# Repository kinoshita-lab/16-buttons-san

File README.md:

# 16-buttons-san

## PCB with 16 buttons and shift registers

"16-buttons-san" is a handy PCB with 16 buttons, and shift resistors and can also cascade next same PCB.

## Kit contents

- Pre-assembled circuit board
- 1x5 pin socket

## How to assemble

Solder the included 1x05 pin socket into the following place below:

## Sample program

Please refer to the exapmles/Simple
<https://github.com/kinoshita-lab/16-buttons-san/tree/main/software/examples/Simple>

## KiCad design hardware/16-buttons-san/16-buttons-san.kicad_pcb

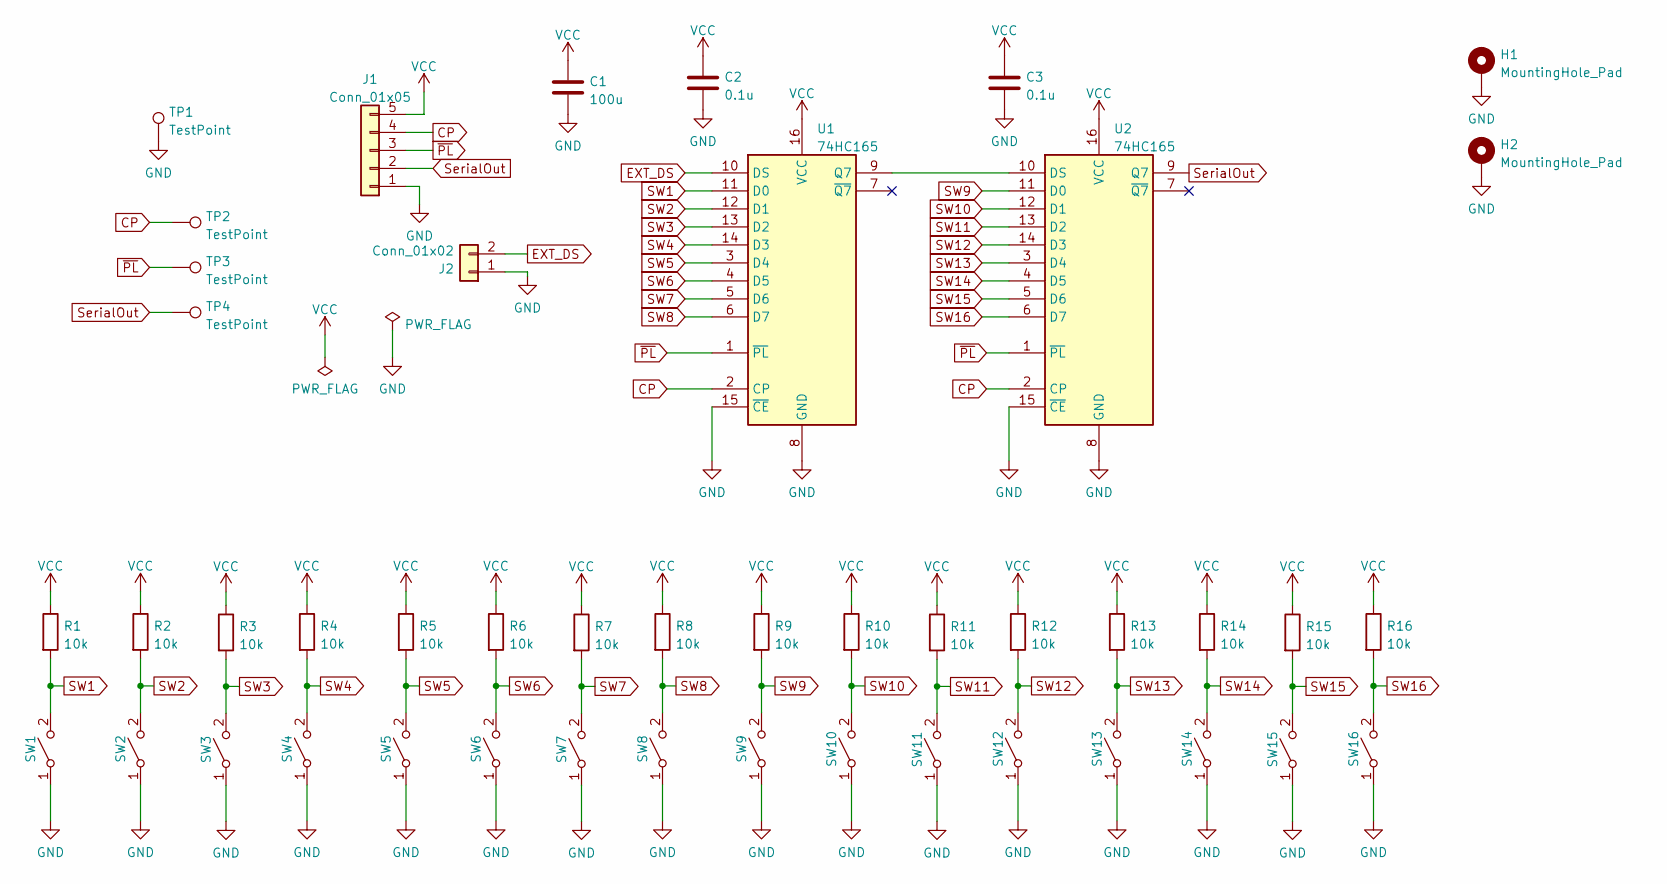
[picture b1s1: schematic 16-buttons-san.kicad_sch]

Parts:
C1: 100u; C_1206_3216Metric_Pad1.33x1.80mm_HandSolder; LCSC C312983
C2, C3: 0.1u; C_0402_1005Metric_Pad0.74x0.62mm_HandSolder; LCSC C1525
H1, H2: MountingHole_Pad; MountingHole_3.2mm_M3_DIN965_Pad
J1: Conn_01x05; PinHeader_1x05_P2.54mm_Vertical
J2: Conn_01x02; PinHeader_1x02_P2.54mm_Vertical
R1, R2, R3, R4, R5, R6, R7, R8, R9, R10, R11, R12, R13, R14, R15, R16: 10k; R_0402_1005Metric_Pad0.72x0.64mm_HandSolder; LCSC C25744
SW1, SW2, SW3, SW4, SW5, SW6, SW7, SW8, SW9, SW10, SW11, SW12, SW13, SW14, SW15, SW16: SW_SPST; SW_Tactile_6mm_x_6mm_Futsuuno_Akizuki_nadoniaruyatsu; LCSC C2828575
TP1, TP2, TP3, TP4: TestPoint; TestPoint_THTPad_D2.0mm_Drill1.0mm
U1, U2: 74HC165; TSSOP-16_4.4x5mm_P0.65mm; LCSC C80696

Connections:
CP: J1.4, TP2.1, U1.2 (CP), U2.2 (CP)
EXT_DS: J2.2, U1.10 (DS)
GND: C1.2, C2.2, C3.2, H1.1, H2.1, J1.1, J2.1, SW1.1 (A), SW2.1 (A), SW3.1 (A), SW4.1 (A), SW5.1 (A), SW6.1 (A), SW7.1 (A), SW8.1 (A), SW9.1 (A), SW10.1 (A), SW11.1 (A), SW12.1 (A), SW13.1 (A), SW14.1 (A), SW15.1 (A), SW16.1 (A), TP1.1, U1.8 (GND), U1.15 (~CE), U2.8 (GND), U2.15 (~CE)
unnamed: U1.9 (Q7), U2.10 (DS)
SW1: R1.2, SW1.2 (B), U1.11 (D0)
SW2: R2.2, SW2.2 (B), U1.12 (D1)
SW3: R3.2, SW3.2 (B), U1.13 (D2)
SW4: R4.2, SW4.2 (B), U1.14 (D3)
SW5: R5.2, SW5.2 (B), U1.3 (D4)
SW6: R6.2, SW6.2 (B), U1.4 (D5)
SW7: R7.2, SW7.2 (B), U1.5 (D6)
SW8: R8.2, SW8.2 (B), U1.6 (D7)
SW9: R9.2, SW9.2 (B), U2.11 (D0)
SW10: R10.2, SW10.2 (B), U2.12 (D1)
SW11: R11.2, SW11.2 (B), U2.13 (D2)
SW12: R12.2, SW12.2 (B), U2.14 (D3)
SW13: R13.2, SW13.2 (B), U2.3 (D4)
SW14: R14.2, SW14.2 (B), U2.4 (D5)
SW15: R15.2, SW15.2 (B), U2.5 (D6)
SW16: R16.2, SW16.2 (B), U2.6 (D7)
SerialOut: J1.2, TP4.1, U2.9 (Q7)
VCC: C1.1, C2.1, C3.1, J1.5, R1.1, R2.1, R3.1, R4.1, R5.1, R6.1, R7.1, R8.1, R9.1, R10.1, R11.1, R12.1, R13.1, R14.1, R15.1, R16.1, U1.16 (VCC), U2.16 (VCC)
~PL: J1.3, TP3.1, U1.1 (~PL), U2.1 (~PL)

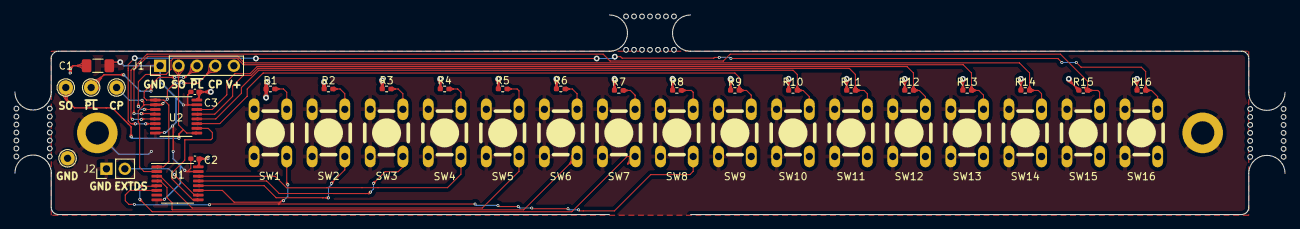
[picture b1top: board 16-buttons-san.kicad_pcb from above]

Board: 2 copper layers, 175.0 x 27.5 mm, 45 parts (0 on the bottom side), 23 nets.

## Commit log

2022-07-10 add software examples
2022-07-10 add hardware files
2022-07-10 add pdf version of schematics and pcbs
2022-09-02 add docs, images
2022-09-02 add docs and samples
2022-09-02 modify ja doc
2022-11-20 Create LICENSE
2025-08-26 Fix critical scan_period_ initialization bug
    - Add missing scan_period_ = scan_period assignment in constructor
    - This fixes timing logic in WaitNext state that was using uninitialized value
    - Add comprehensive efficiency analysis report documenting 5 improvement areas
    - Critical bug caused continuous scanning without proper delays
